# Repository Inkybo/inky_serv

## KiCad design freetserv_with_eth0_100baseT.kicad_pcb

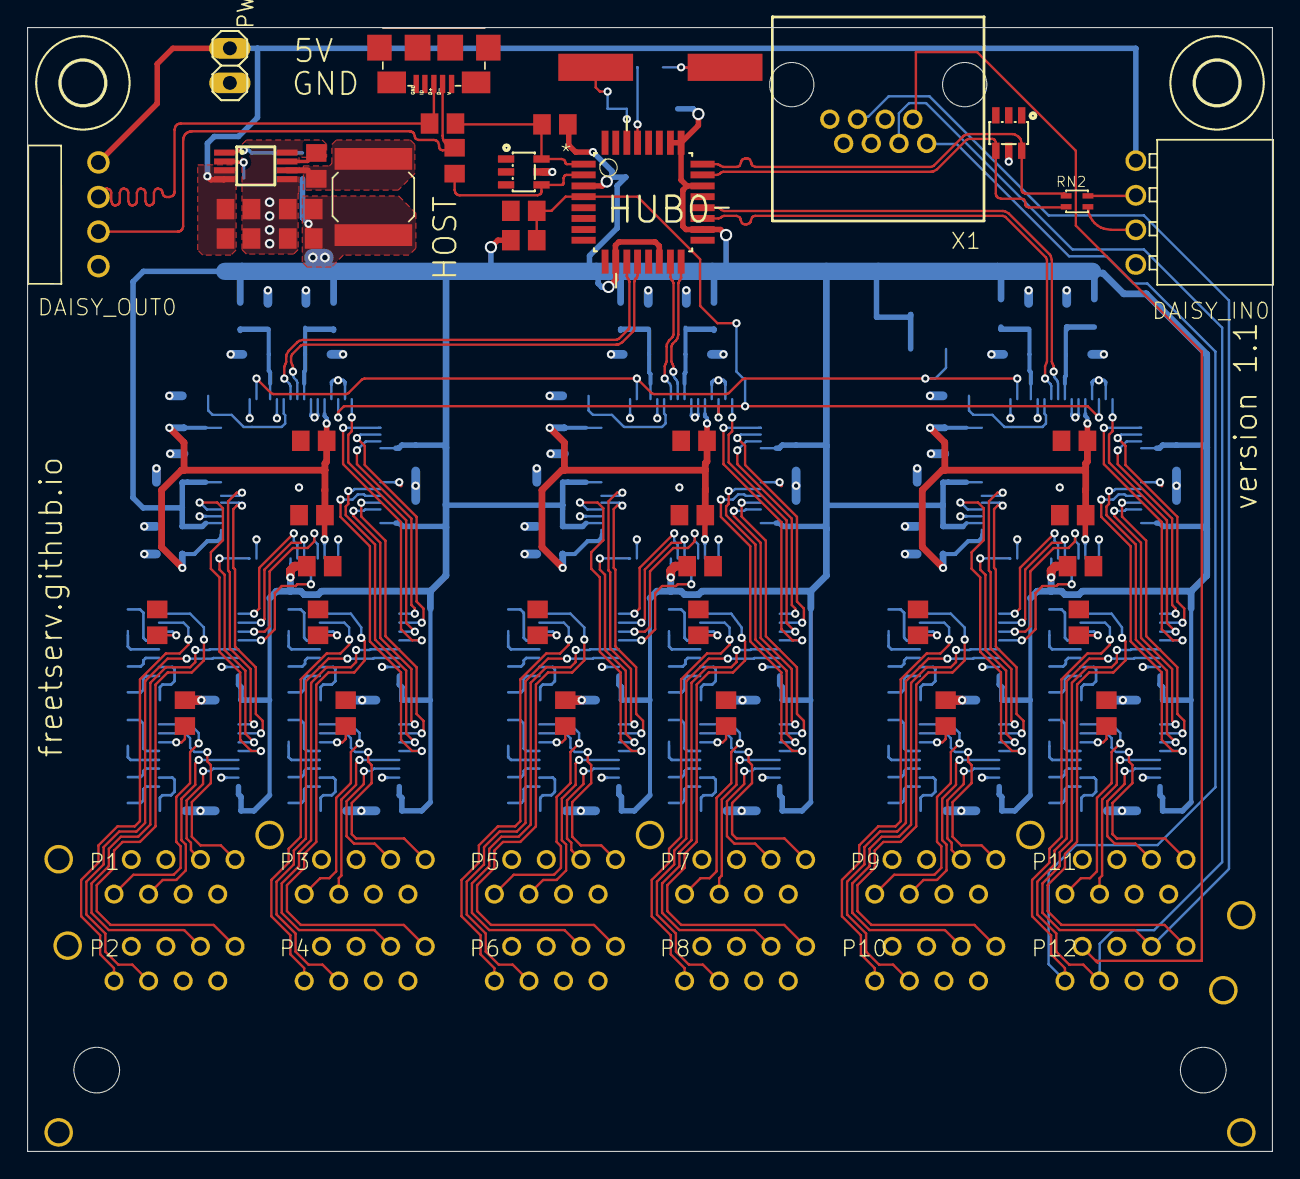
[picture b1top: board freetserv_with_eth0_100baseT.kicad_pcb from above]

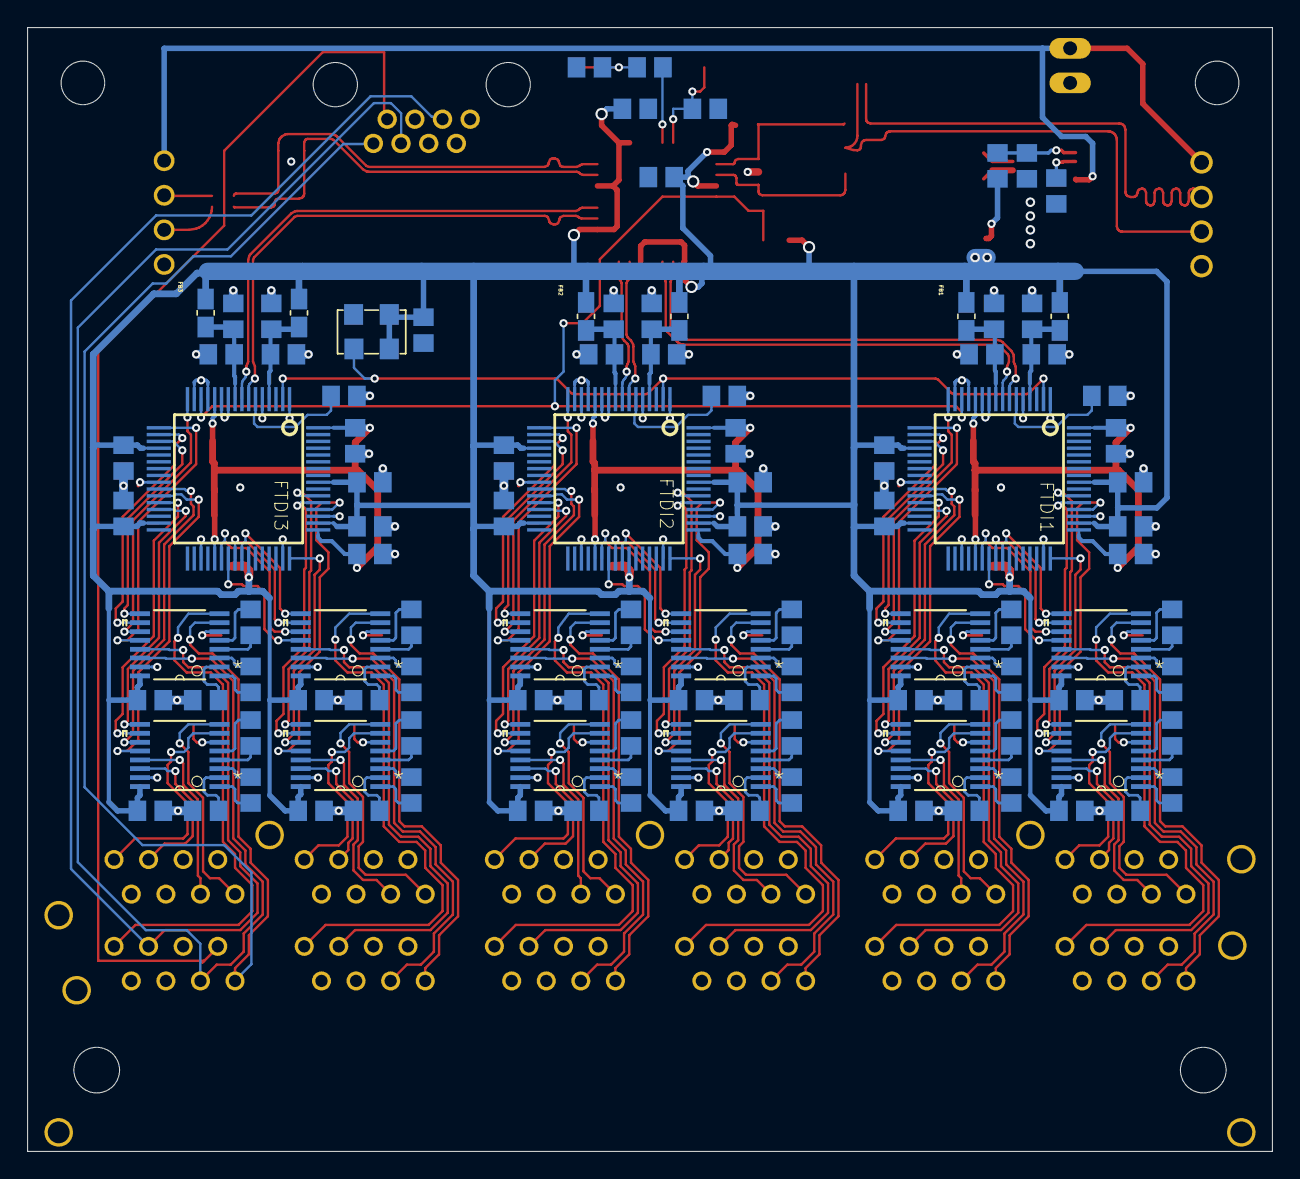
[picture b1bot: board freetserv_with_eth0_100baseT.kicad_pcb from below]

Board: 16 copper layers, 91.4 x 82.6 mm, 158 parts (112 on the bottom side), 207 nets.

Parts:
C1, C4, C11, C12, C15, C16, C17, C18, C19, C22, C23, C24, C25, C26, C27, C28, C29, C30, C31, C32, C33, C34, C35, C36, C37, C38, C39, C40, C41, C42, C43, C44, C45, C46, C47, C54, C55, C56, C57, C58, C59, C60, C61, C62, C63, C64, C65, C66, C67, C68, C69, C70, C71, C72, C73, C74, C75, C76, C77, C78, C79, C80, C81, C89, C90, C91, C92, C93, C94, C95, C96, C97, C98, C99, C100, C101, C102, C103, C104, C105, C106, C107, C108, C109, C110, C111, C112, C113, C114, C115, C116, C489, C519, C859, C869: 0.1uF; C0805
C2, C3, C6, C7: 10uF; C0805
C5: 1uF; C0805
C8, C629, C829: 3.3uF; C0805
C13, C14, C53, C502, C879, C889: 4.7uF; C0805
C20, C21: 18pF; C0805
D1, D2: SN65220; SOT23-6
DAISY_IN0: 613004143121
DAISY_OUT0: 61300411021
FB1, FB2, FB2\0, FB2\1, FB2\2, FB3: 330; WE-KI_0805A
FTDI1, FTDI2, FTDI3: FT4232HL; LQFP64
H1, H2: MOUNT-HOLE3.2; 3,2
HUB0: TUSB2046BVF; QFP80P900X900X145-32N
IC1: MCP16311; MSOP8
IC5, IC6, IC7, IC8, IC10, IC11, IC12, IC13, IC15, IC16, IC17, IC18: 3232; SOP65P640X120-16N
L3: 15uH; NR60XX
PWRIN0: 1X02
Q2: 6MHz; CSM-7X-DU
QG1: ASFL1-12.000; XO53
R1, R8: 27; R0805
R2, R13, R15: 12K/1%; R0805
R3, R6: 1.5K; R0805
R4: 31.6k; R0805
R5: 10k; R0805
R7: 22K; R0805
RN2: 27; EXBV4V
U$1: SS73100-046F_DWG; SS73100-046F
USB_HOST0: USB_MICROB; USB_MICROB_PACKAGE
X1: 0446200001

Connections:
12MHZ: FTDI1.2, FTDI2.2, FTDI3.2, QG1.3
+1V8-1: C8.2, C38.1, C39.1, C40.1, FTDI1.12, FTDI1.37, FTDI1.49, FTDI1.64
+1V8-2: C59.1, C60.1, C61.1, C629.2, FTDI2.12, FTDI2.37, FTDI2.49, FTDI2.64
+1V8-3: C94.1, C95.1, C96.1, C829.2, FTDI3.12, FTDI3.37, FTDI3.49, FTDI3.64
+3V3: C6.1, C7.1, C19.2, C25.2, C30.2, C35.2, C36.2, C41.1, C42.1, C43.1, C44.1, C45.1, C46.2, C47.2, C58.2, C62.1, C63.1, C64.1, C65.1, C66.1, C71.2, C76.2, C81.2, C93.2, C97.1, C98.1, C99.1, C100.1, C101.1, C106.2, C111.2, C116.2, FB1.1, FB2.1, FB2\0.1, FB2\1.1, FB2\2.1, FB3.1, FTDI1.20, FTDI1.31, FTDI1.42, FTDI1.50, FTDI1.56, FTDI2.20, FTDI2.31, FTDI2.42, FTDI2.50, FTDI2.56, FTDI3.20, FTDI3.31, FTDI3.42, FTDI3.50, FTDI3.56, HUB0.3, HUB0.10, HUB0.14, HUB0.18, HUB0.22, HUB0.25, HUB0.26, IC5.16, IC6.16, IC7.16, IC8.16, IC10.16, IC11.16, IC12.16, IC13.16, IC15.16, IC16.16, IC17.16, IC18.16, L3.2, QG1.1, QG1.4, R4.1, R6.1, R7.2
+5V: C2.1, C3.1, DAISY_IN0.1, DAISY_OUT0.1, IC1.3, IC1.4, PWRIN0.1
CTS1E: IC5.8, U$1.P4.8
CTS1E1: IC10.8, U$1.P8.8
CTS1E2: IC15.8, U$1.P12.8
CTS1I: FTDI1.19, IC5.9
CTS1I1: FTDI2.19, IC10.9
CTS1I2: FTDI3.19, IC15.9
CTS2E: IC6.8, U$1.P3.8
CTS2E1: IC11.8, U$1.P7.8
CTS2E2: IC16.8, U$1.P11.8
CTS2I: FTDI1.29, IC6.9
CTS2I1: FTDI2.29, IC11.9
CTS2I2: FTDI3.29, IC16.9
CTS3E: IC7.8, U$1.P2.8
CTS3E1: IC12.8, U$1.P6.8
CTS3E2: IC17.8, U$1.P10.8
CTS3I: FTDI1.41, IC7.9
CTS3I1: FTDI2.41, IC12.9
CTS3I2: FTDI3.41, IC17.9
CTS4E: IC8.8, U$1.P1.8
CTS4E1: IC13.8, U$1.P5.8
CTS4E2: IC18.8, U$1.P9.8
CTS4I: FTDI1.54, IC8.9
CTS4I1: FTDI2.54, IC13.9
CTS4I2: FTDI3.54, IC18.9
D0_N: D1.4, HUB0.2, R1.1
D0_P: D1.6, HUB0.1, R6.2, R8.1
D1_N: D2.4, HUB0.23, RN2.B1
D1_P: D2.6, HUB0.24, RN2.A1
D2_N: FTDI1.7, HUB0.11
D2_P: FTDI1.8, HUB0.12
D3_N: FTDI2.7, HUB0.15
D3_P: FTDI2.8, HUB0.16
D4_N: FTDI3.7, HUB0.19
D4_P: FTDI3.8, HUB0.20
DX0_N: DAISY_OUT0.3, R1.2, USB_HOST0.D-
DX0_P: DAISY_OUT0.2, R8.2, USB_HOST0.D+
ETXN: U$1.P12.2, X1.2
GND: C2.2, C3.2, C5.2, C6.2, C7.2, C8.1, C11.2, C12.2, C13.2, C14.2, C17.1, C18.1, C19.1, C20.1, C21.1, C23.1, C24.1, C25.1, C28.1, C29.1, C30.1, C33.1, C34.1, C35.1, C36.1, C37.1, C38.2, C39.2, C40.2, C41.2, C42.2, C43.2, C44.2, C45.2, C46.1, C47.1, C53.2, C56.1, C57.1, C58.1, C59.2, C60.2, C61.2, C62.2, C63.2, C64.2, C65.2, C66.2, C69.1, C70.1, C71.1, C74.1, C75.1, C76.1, C79.1, C80.1, C81.1, C91.1, C92.1, C93.1, C94.2, C95.2, C96.2, C97.2, C98.2, C99.2, C100.2, C101.2, C104.1, C105.1, C106.1, C109.1, C110.1, C111.1, C114.1, C115.1, C116.1, C489.2, C502.2, C519.2, C629.1, C829.1, C859.2, C869.2, C879.2, C889.2, D1.2, D1.5, D2.2, D2.5, DAISY_IN0.4, DAISY_OUT0.4, FTDI1.1, FTDI1.5, FTDI1.10, FTDI1.11, FTDI1.13, FTDI1.15, FTDI1.25, FTDI1.35, FTDI1.47, FTDI1.51, FTDI2.1, FTDI2.5, FTDI2.10, FTDI2.11, FTDI2.13, FTDI2.15, FTDI2.25, FTDI2.35, FTDI2.47, FTDI2.51, FTDI3.1, FTDI3.5, FTDI3.10, FTDI3.11, FTDI3.13, FTDI3.15, FTDI3.25, FTDI3.35, FTDI3.47, FTDI3.51, HUB0.7, HUB0.8, HUB0.27, HUB0.28, HUB0.31, IC1.5, IC1.8, IC5.15, IC6.15, IC7.15, IC8.15, IC10.15, IC11.15, IC12.15, IC13.15, IC15.15, IC16.15, IC17.15, IC18.15, PWRIN0.2, QG1.2, R2.1, R5.2, R13.1, R15.1, U$1.P1.4, U$1.P1.5, U$1.P2.4, U$1.P2.5, U$1.P3.4, U$1.P3.5, U$1.P4.4, U$1.P4.5, U$1.P5.4, U$1.P5.5, U$1.P6.4, U$1.P6.5, U$1.P7.4, U$1.P7.5, U$1.P8.4, U$1.P8.5, U$1.P9.4, U$1.P9.5, U$1.P10.4, U$1.P10.5, U$1.P11.4, U$1.P11.5, U$1.P12.4, U$1.P12.5, USB_HOST0.GND
unnamed: C1.2, IC6.1
unnamed: C1.1, IC6.3
unnamed: C4.1, IC1.7
unnamed: C4.2, IC1.6, L3.1
unnamed: FTDI2.6, R13.2
unnamed: IC1.1, R4.2, R5.1
unnamed: DAISY_IN0.2, RN2.A2
unnamed: DAISY_IN0.3, RN2.B2
unnamed: C5.1, IC1.2
unnamed: C22.2, IC6.4
unnamed: C22.1, IC6.5
unnamed: FTDI1.6, R2.2
unnamed: C11.1, C13.1, FB2\0.2, FTDI1.4
unnamed: C12.1, C14.1, FB1.2, FTDI1.9
unnamed: C54.2, IC10.1
unnamed: C54.1, IC10.3
unnamed: C23.2, IC6.2
unnamed: C24.2, IC6.6
unnamed: C55.2, IC10.4
unnamed: C55.1, IC10.5
unnamed: C56.2, IC10.2
unnamed: C57.2, IC10.6
unnamed: C67.2, IC11.1
unnamed: C67.1, IC11.3
unnamed: C68.2, IC11.4
unnamed: C68.1, IC11.5
unnamed: C15.2, IC5.1
unnamed: C15.1, IC5.3
unnamed: C16.2, IC5.4
unnamed: C16.1, IC5.5
unnamed: C69.2, IC11.2
unnamed: C70.2, IC11.6
unnamed: HUB0.29, R3.1
unnamed: C72.2, IC12.1
unnamed: C17.2, IC5.2
unnamed: C18.2, IC5.6
unnamed: C72.1, IC12.3
unnamed: C73.2, IC12.4
unnamed: C73.1, IC12.5
unnamed: C20.2, HUB0.30, Q2.1
unnamed: C21.2, Q2.2, R3.2
unnamed: C26.2, IC7.1
unnamed: C26.1, IC7.3
unnamed: C27.2, IC7.4
unnamed: C27.1, IC7.5
unnamed: C74.2, IC12.2
unnamed: C75.2, IC12.6
unnamed: C28.2, IC7.2
unnamed: C29.2, IC7.6
unnamed: C77.1, IC13.3
unnamed: C78.2, IC13.4
unnamed: C78.1, IC13.5
unnamed: C79.2, IC13.2
unnamed: C80.2, IC13.6
unnamed: C31.2, IC8.1
unnamed: C31.1, IC8.3
unnamed: C32.2, IC8.4
unnamed: C32.1, IC8.5
unnamed: FTDI3.6, R15.2
unnamed: C33.2, IC8.2
unnamed: C34.2, IC8.6
unnamed: C859.1, C879.1, FB2\2.2, FTDI3.4
unnamed: C869.1, C889.1, FB3.2, FTDI3.9
unnamed: C89.2, IC15.1
unnamed: C89.1, IC15.3
unnamed: C90.2, IC15.4
unnamed: C90.1, IC15.5
unnamed: C91.2, IC15.2
unnamed: C92.2, IC15.6
unnamed: C102.2, IC16.1
unnamed: C102.1, IC16.3
unnamed: C103.2, IC16.4
unnamed: C103.1, IC16.5
unnamed: C104.2, IC16.2
unnamed: C105.2, IC16.6
unnamed: C107.2, IC17.1
unnamed: C107.1, IC17.3
unnamed: C108.2, IC17.4
unnamed: C108.1, IC17.5
unnamed: C109.2, IC17.2
unnamed: C110.2, IC17.6
unnamed: C112.2, IC18.1
unnamed: C112.1, IC18.3
unnamed: C113.2, IC18.4
unnamed: C113.1, IC18.5
unnamed: C114.2, IC18.2
unnamed: C115.2, IC18.6
unnamed: C489.1, C502.1, FB2\1.2, FTDI2.4
unnamed: C53.1, C519.1, FB2.2, FTDI2.9
unnamed: C77.2, IC13.1
RTS1E: IC5.7, U$1.P4.1
RTS1E1: IC10.7, U$1.P8.1
RTS1E2: IC15.7, U$1.P12.1, X1.1
RTS1I: FTDI1.18, IC5.10
RTS1I1: FTDI2.18, IC10.10
RTS1I2: FTDI3.18, IC15.10
RTS2E: IC6.7, U$1.P3.1
RTS2E1: IC11.7, U$1.P7.1
RTS2E2: IC16.7, U$1.P11.1
RTS2I: FTDI1.28, IC6.10
RTS2I1: FTDI2.28, IC11.10
RTS2I2: FTDI3.28, IC16.10
RTS3E: IC7.7, U$1.P2.1
RTS3E1: IC12.7, U$1.P6.1
RTS3E2: IC17.7, U$1.P10.1
RTS3I: FTDI1.40, IC7.10
RTS3I1: FTDI2.40, IC12.10
RTS3I2: FTDI3.40, IC17.10
RTS4E: IC8.7, U$1.P1.1
RTS4E1: IC13.7, U$1.P5.1
RTS4E2: IC18.7, U$1.P9.1
RTS4I: FTDI1.53, IC8.10
RTS4I1: FTDI2.53, IC13.10
RTS4I2: FTDI3.53, IC18.10
RXD1E: IC5.13, U$1.P4.6
RXD1E1: IC10.13, U$1.P8.6
RXD1E2: IC15.13, U$1.P12.6, X1.6
RXD1I: FTDI1.17, IC5.12
RXD1I1: FTDI2.17, IC10.12
RXD1I2: FTDI3.17, IC15.12
RXD2E: IC6.13, U$1.P3.6
RXD2E1: IC11.13, U$1.P7.6
RXD2E2: IC16.13, U$1.P11.6
RXD2I: FTDI1.27, IC6.12
RXD2I1: FTDI2.27, IC11.12
RXD2I2: FTDI3.27, IC16.12
RXD3E: IC7.13, U$1.P2.6
RXD3E1: IC12.13, U$1.P6.6
RXD3E2: IC17.13, U$1.P10.6
RXD3I: FTDI1.39, IC7.12
RXD3I1: FTDI2.39, IC12.12
RXD3I2: FTDI3.39, IC17.12
RXD4E: IC8.13, U$1.P1.6
RXD4E1: IC13.13, U$1.P5.6
RXD4E2: IC18.13, U$1.P9.6
RXD4I: FTDI1.52, IC8.12
RXD4I1: FTDI2.52, IC13.12
RXD4I2: FTDI3.52, IC18.12
TXD1E: IC5.14, U$1.P4.3
TXD1E1: IC10.14, U$1.P8.3
TXD1E2: IC15.14, U$1.P12.3, X1.3
TXD1I: FTDI1.16, IC5.11
TXD1I1: FTDI2.16, IC10.11
TXD1I2: FTDI3.16, IC15.11
TXD2E: IC6.14, U$1.P3.3
TXD2E1: IC11.14, U$1.P7.3
TXD2E2: IC16.14, U$1.P11.3
TXD2I: FTDI1.26, IC6.11
TXD2I1: FTDI2.26, IC11.11
TXD2I2: FTDI3.26, IC16.11
TXD3E: IC7.14, U$1.P2.3
TXD3E1: IC12.14, U$1.P6.3
TXD3E2: IC17.14, U$1.P10.3
TXD3I: FTDI1.38, IC7.11
TXD3I1: FTDI2.38, IC12.11
TXD3I2: FTDI3.38, IC17.11
TXD4E: IC8.14, U$1.P1.3
TXD4E1: IC13.14, U$1.P5.3
TXD4E2: IC18.14, U$1.P9.3
TXD4I: FTDI1.48, IC8.11
TXD4I1: FTDI2.48, IC13.11
TXD4I2: FTDI3.48, IC18.11
~RESET: C37.2, FTDI1.14, FTDI2.14, FTDI3.14, HUB0.4, R7.1

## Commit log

2025-05-30 port pcb files to kicad
2025-05-30 fixed .gitignore
